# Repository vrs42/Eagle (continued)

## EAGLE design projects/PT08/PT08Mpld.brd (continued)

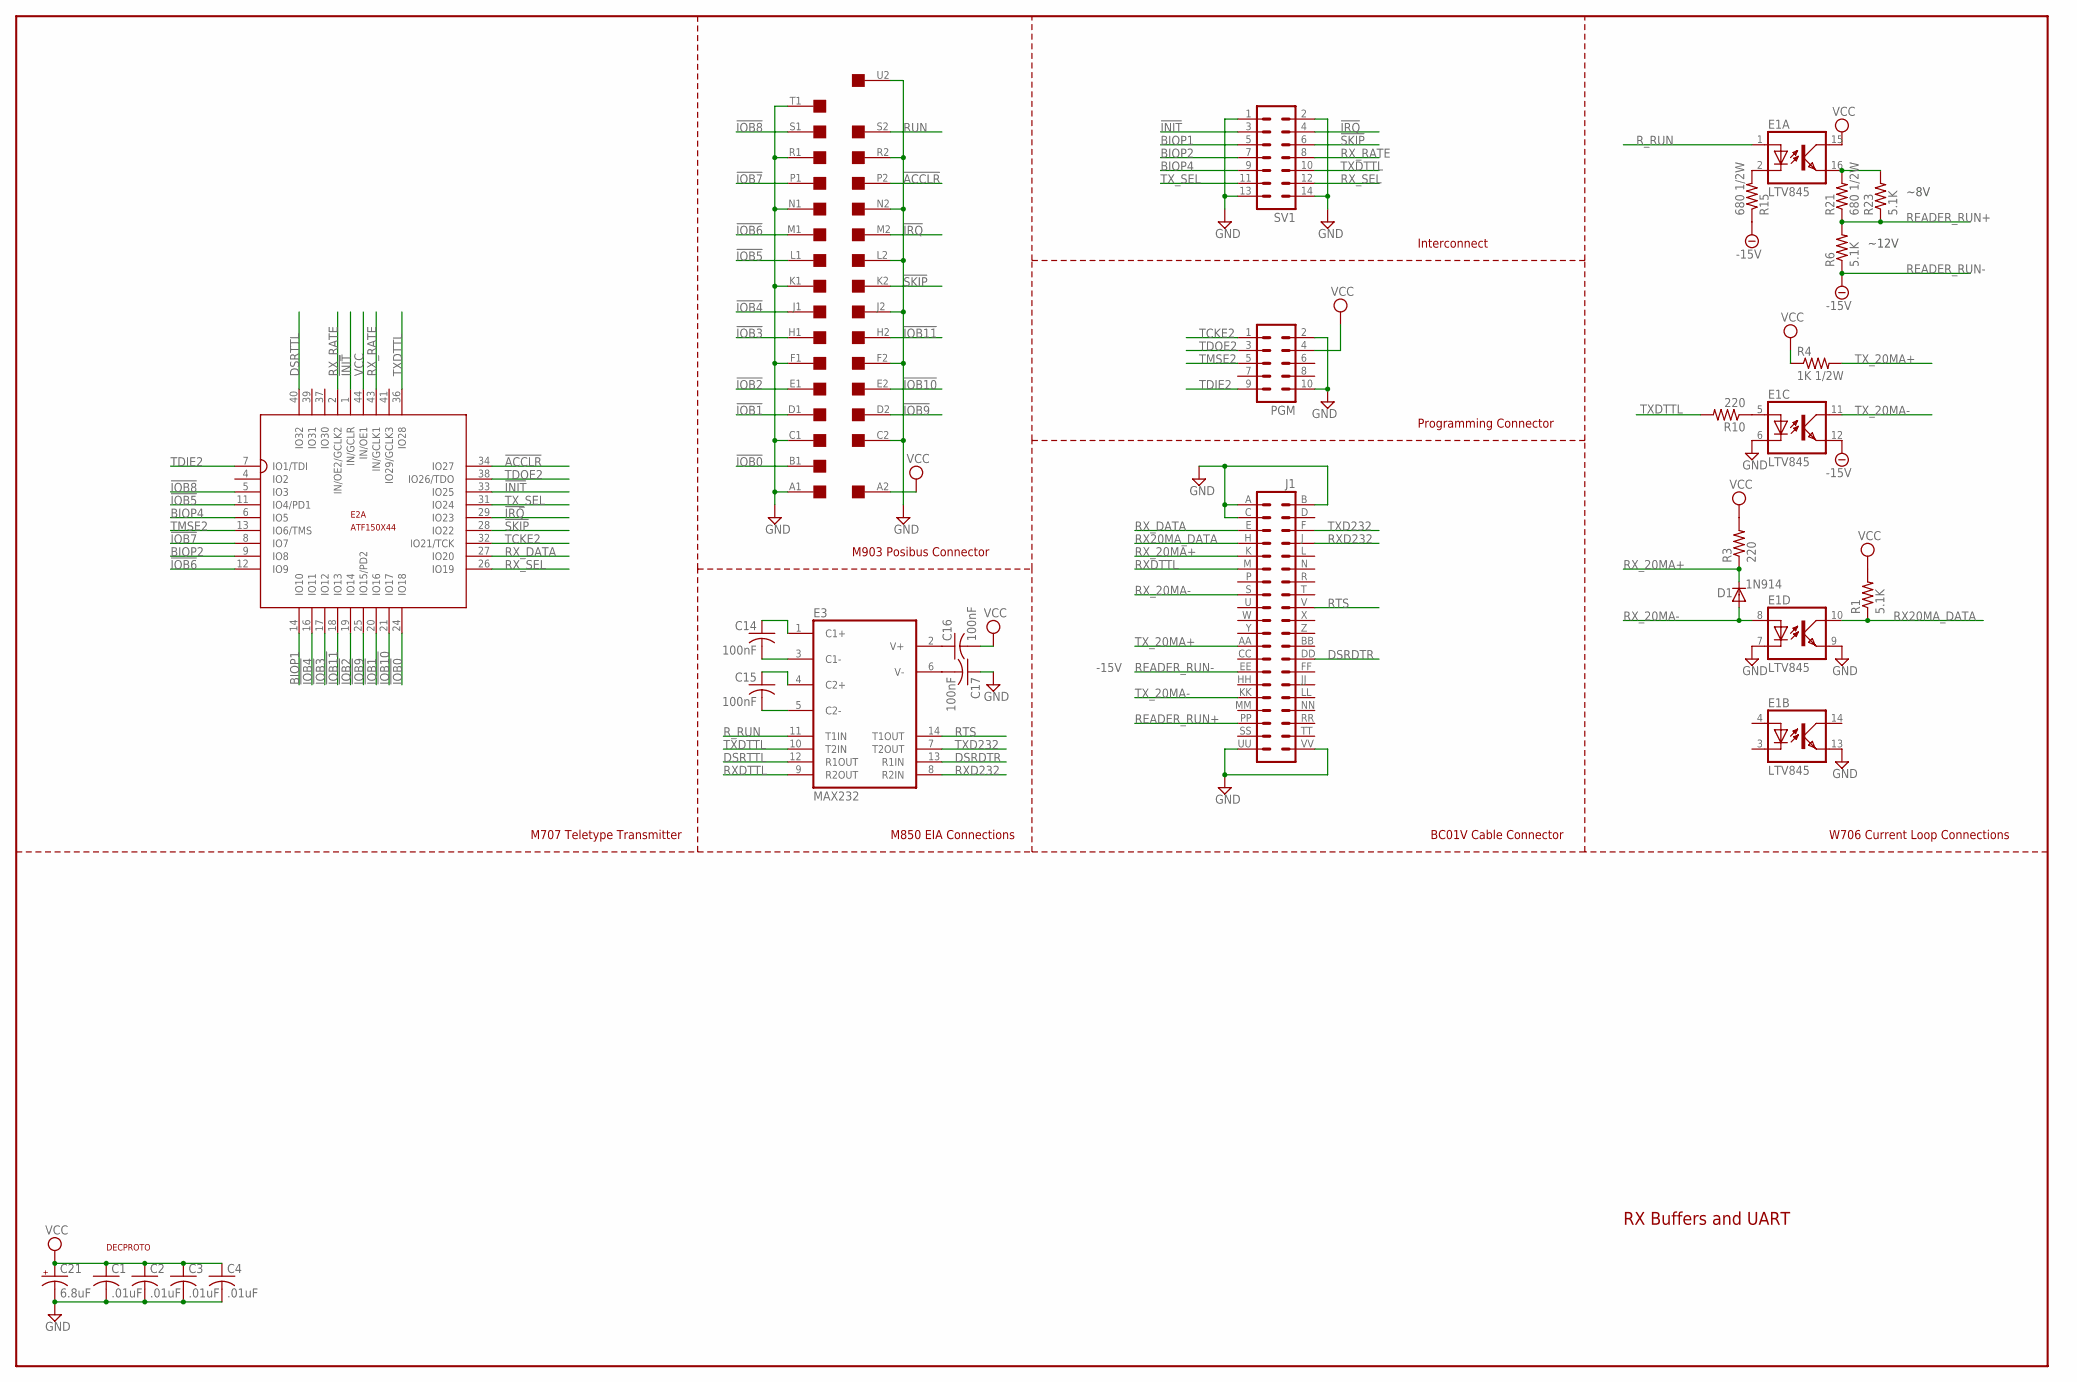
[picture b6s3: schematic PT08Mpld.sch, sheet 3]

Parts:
C1, C2, C3, C4: .01uF; C050-025X075
C14, C15, C16, C17: 100nF; C050-025X075
C21: 6.8uF; E12-8
D1: 1N914; DO41-10
E1: LTV845; DIL16
E2: ATF150X44; 3M44
E3: MAX232; DIL16
IOB: EDGE-2CONNECTOR; EDGE-CON2
J1: DEC40PINH
PGM: ML10
R1, R6, R23: 5.1K; 0207/10
R3, R10: 220; 0207/10
R4: 1K 1/2W; 0207/12
R15, R21: 680 1/2W; 0207/12
SV1: ML14L
U$2: DECPROTO; DECPROTO111

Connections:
!ACCLR: E2.34 (IO27), IOB.P2
!INIT: E2.1 (IN/GCLR), E2.33 (IO25), SV1.3; also elsewhere on the board
!IOB0: E2.24 (IO18), IOB.B1
!IOB1: E2.20 (IO16), IOB.D1
!IOB2: E2.19 (IO14), IOB.E1
!IOB3: E2.17 (IO12), IOB.H1
!IOB4: E2.16 (IO11), IOB.J1
!IOB5: E2.11 (IO4/PD1), IOB.L1
!IOB6: E2.12 (IO9), IOB.M1
!IOB7: E2.8 (IO7), IOB.P1
!IOB8: E2.5 (IO3), IOB.S1
!IOB9: E2.25 (IO15/PD2), IOB.D2
!IOB10: E2.21 (IO17), IOB.E2
!IOB11: E2.18 (IO13), IOB.H2
!IRQ: E2.29 (IO23), IOB.M2, SV1.4; also elsewhere on the board
!SKIP: E2.28 (IO22), IOB.K2, SV1.6; also elsewhere on the board
-15V: E1.12 (EMIT), J1.EE (27), R6.1, R15.1
BIOP1: E2.14 (IO10), SV1.5; also elsewhere on the board
BIOP2: E2.9 (IO8), SV1.7; also elsewhere on the board
BIOP4: E2.6 (IO5), SV1.9; also elsewhere on the board
DSRDTR: E3.13 (R1IN), J1.DD (26)
DSRTTL: E2.40 (IO32), E3.12 (R1OUT)
GND: C1.2, C2.2, C3.2, C4.2, C17.1, C21.-, E1.6 (C), E1.7 (C), E1.9 (EMIT), E1.13 (EMIT), E2.10 (GND), E2.22 (GND), E2.30 (GND), E2.42 (GND), E3.15 (GND), IOB.A1, IOB.C1, IOB.C2, IOB.F1, IOB.F2, IOB.J2, IOB.K1, IOB.L2, IOB.N1, IOB.N2, IOB.R1, IOB.R2, IOB.T1, IOB.U2, J1.A (1), J1.B (2), J1.C (3), J1.UU (39), J1.VV (40), PGM.2, PGM.10, SV1.1, SV1.2, SV1.13, SV1.14; also elsewhere on the board
unnamed: E1.2 (C), R15.2
unnamed: E1.16 (EMIT), R21.2, R23.2
unnamed: E1.5 (A), R10.1
unnamed: C17.2, E3.6 (V-)
unnamed: C14.1, E3.1 (C1+)
unnamed: C14.2, E3.3 (C1-)
unnamed: C15.2, E3.5 (C2-)
unnamed: C15.1, E3.4 (C2+)
unnamed: C16.1, E3.2 (V+)
READER_RUN+: J1.PP (35), R6.2, R21.1, R23.1
RTS: E3.14 (T1OUT), J1.V (18)
RUN: IOB.S2
RX20MA_DATA: E1.10 (COL), J1.H (7), R1.1
RXD232: E3.8 (R2IN), J1.J (8)
RXDTTL: E3.9 (R2OUT), J1.M (11)
RX_20MA+: D1.C, J1.K (9), R3.1
RX_20MA-: D1.A, E1.8 (A), J1.S (15)
RX_DATA: E2.27 (IO20), J1.E (5)
RX_RATE: E2.2 (IN/OE2/GCLK2), E2.43 (IN/GCLK1), SV1.8; also elsewhere on the board
RX_SEL: E2.26 (IO19), SV1.12; also elsewhere on the board
R_RUN: E1.1 (A), E3.11 (T1IN)
TCKE2: E2.32 (IO21/TCK), PGM.1
TDIE2: E2.7 (IO1/TDI), PGM.9
TDOE2: E2.38 (IO26/TDO), PGM.3
TMSE2: E2.13 (IO6/TMS), PGM.5
TXD232: E3.7 (T2OUT), J1.F (6)
TXDTTL: E2.36 (IO28), E3.10 (T2IN), R10.2, SV1.10; also elsewhere on the board
TX_20MA+: J1.AA (23), R4.2
TX_20MA-: E1.11 (COL), J1.KK (31)
TX_SEL: E2.31 (IO24), SV1.11; also elsewhere on the board
VCC: C1.1, C2.1, C3.1, C4.1, C16.2, C21.+, E1.15 (COL), E2.3 (VCC), E2.15 (VCC), E2.23 (VCC), E2.35 (VCC), E2.44 (IN/OE1), E3.16 (VCC), IOB.A2, PGM.4, R1.2, R3.2, R4.1; also elsewhere on the board

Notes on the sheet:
RX Buffers and UART
M707 Teletype Transmitter
M903 Posibus Connector
M850 EIA Connections
W706 Current Loop Connections
~8V
~12V
READER_RUN-
BC01V Cable Connector
Programming Connector
Interconnect

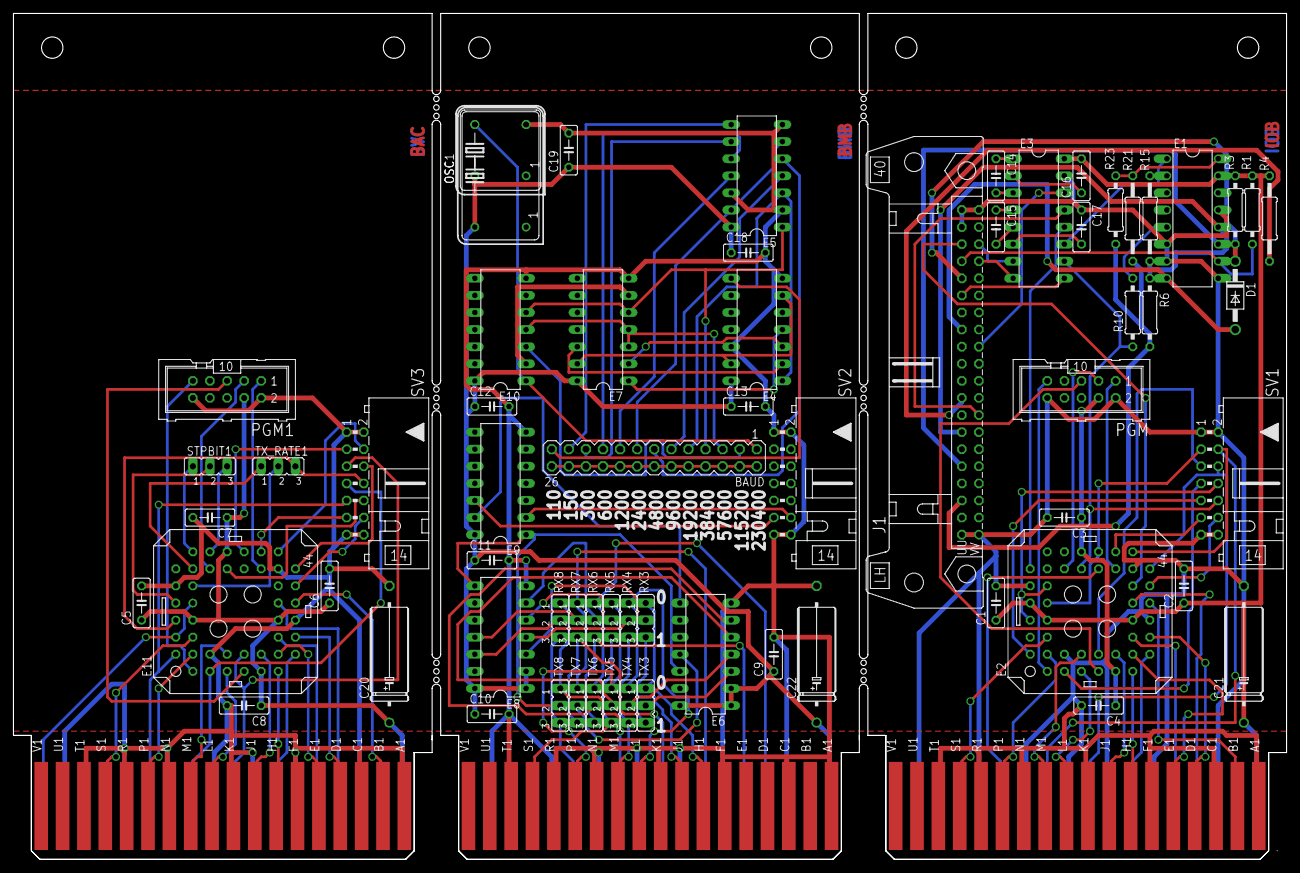
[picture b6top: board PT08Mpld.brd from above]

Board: 4 copper layers, 189.2 x 125.7 mm, 69 parts (0 on the bottom side), 120 nets.
